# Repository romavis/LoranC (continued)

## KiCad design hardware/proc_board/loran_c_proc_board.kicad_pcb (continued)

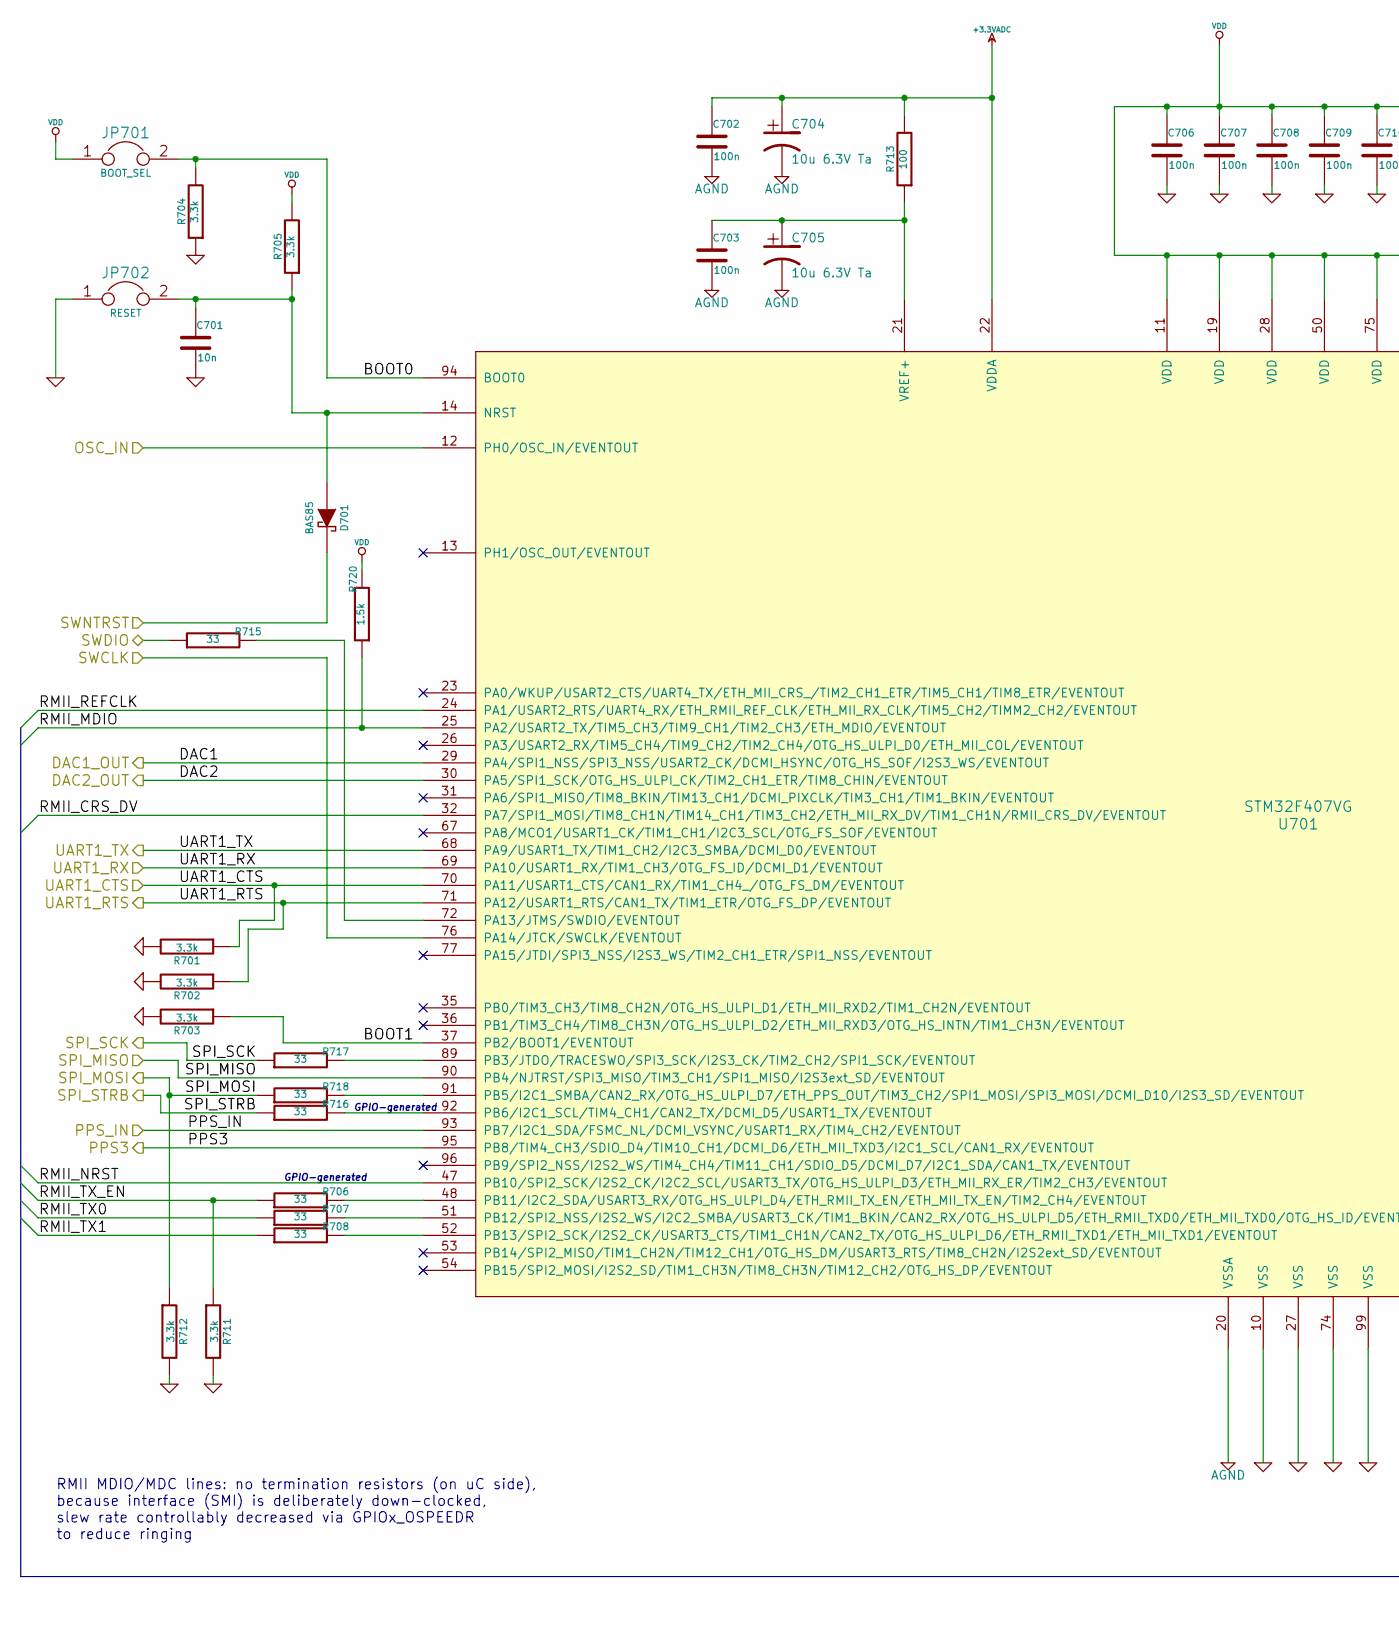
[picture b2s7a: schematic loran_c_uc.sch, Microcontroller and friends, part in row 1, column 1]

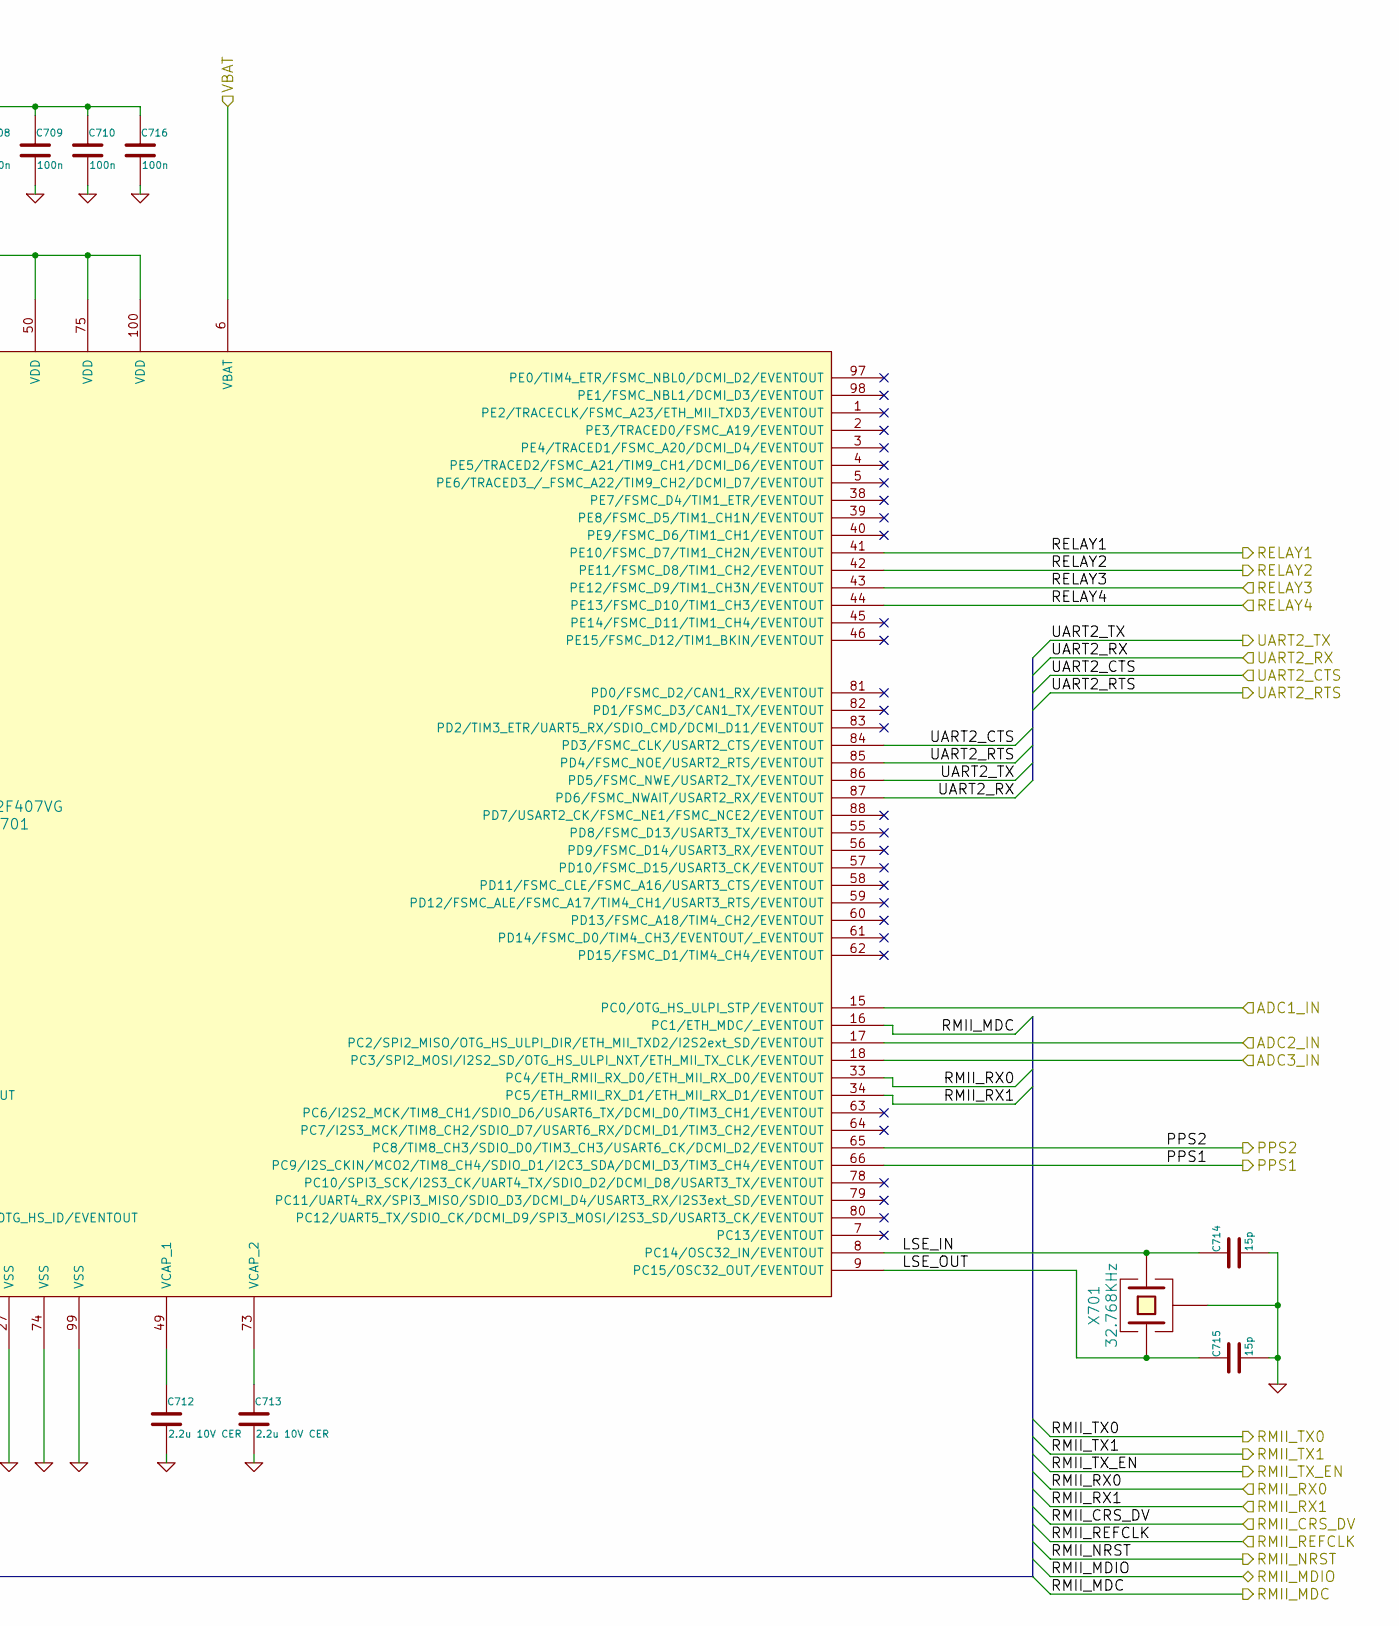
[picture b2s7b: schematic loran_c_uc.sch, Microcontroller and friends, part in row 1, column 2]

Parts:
C701: 10n; c_1206
C702, C703: 100n; c_1206
C704, C705: 10u 6.3V Ta; c_tant_B
C706, C707, C708, C709, C710, C716: 100n; c_0805
C712, C713: 2.2u 10V CER; c_1206
C714, C715: 15p; c_1206
D701: BAS85; sod80c
JP701: BOOT_SEL; Pin_Header_Straight_1x02
JP702: RESET; Pin_Header_Straight_1x02
R701, R702, R705, R711, R712: 3.3k; r_1206
R703, R704: 3.3k; r_0805
R706, R707, R708, R715: 33; r_0805
R713: 100; r_0805
R716, R717, R718: 33; r_1206
R720: 1.5k; r_1206
U701: STM32F407VG; TQFP-100
X701: 32.768KHz; crystal_tc-38_horiz

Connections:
+3.3VADC: C702.1, C704.1, R713.2, U701.22 (VDDA); also elsewhere on the board
/Analog part/DAC1_IN: U701.29 (PA4/SPI1_NSS/SPI3_NSS/USART2_CK/DCMI_HS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); also elsewhere on the board
/Analog part/DAC2_IN: U701.30 (PA5/SPI1_SCK/OTG_HS_ULPI_CK/TIM2_CH1_ET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); also elsewhere on the board
/Ethernet PHY/RMII_CRS_DV: U701.32 (PA7/SPI1_MOSI/TIM8_CH1N/TIM14_CH1/TIM3_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); also elsewhere on the board
/Ethernet PHY/RMII_MDC: U701.16 (PC1/ETH_MDC/_EVENTOUT); also elsewhere on the board
/Ethernet PHY/RMII_MDIO: R720.1, U701.25 (PA2/USART2_TX/TIM5_CH3/TIM9_CH1/TIM2_CH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); also elsewhere on the board
/Ethernet PHY/RMII_NRST: U701.47 (PB10/SPI2_SCK/I2S2_CK/I2C2_SCL/USART3_T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); also elsewhere on the board
/Ethernet PHY/RMII_REFCLK: U701.24 (PA1/USART2_RTS/UART4_RX/ETH_RMII_REF_CL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); also elsewhere on the board
/Ethernet PHY/RMII_RX0: U701.33 (PC4/ETH_RMII_RX_D0/ETH_MII_RX_D0/EVENTO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); also elsewhere on the board
/Ethernet PHY/RMII_RX1: U701.34 (PC5/ETH_RMII_RX_D1/ETH_MII_RX_D1/EVENTO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); also elsewhere on the board
/Ethernet PHY/RMII_TX0: R707.1; also elsewhere on the board
/Ethernet PHY/RMII_TX1: R708.1; also elsewhere on the board
/Ethernet PHY/RMII_TX_EN: R706.1, R711.1; also elsewhere on the board
/RS232 interface/UART1_CTS: R701.1, U701.70 (PA11/USART1_CTS/CAN1_RX/TIM1_CH4_/OTG_F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); also elsewhere on the board
/RS232 interface/UART1_RTS: R702.1, U701.71 (PA12/USART1_RTS/CAN1_TX/TIM1_ETR/OTG_FS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); also elsewhere on the board
/RS232 interface/UART1_RX: U701.69 (PA10/USART1_RX/TIM1_CH3/OTG_FS_ID/DCMI_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); also elsewhere on the board
/RS232 interface/UART1_TX: U701.68 (PA9/USART1_TX/TIM1_CH2/I2C3_SMBA/DCMI_D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); also elsewhere on the board
/RS232 interface/UART2_CTS: U701.84 (PD3/FSMC_CLK/USART2_CTS/EVENTOUT); also elsewhere on the board
/RS232 interface/UART2_RTS: U701.85 (PD4/FSMC_NOE/USART2_RTS/EVENTOUT); also elsewhere on the board
/RS232 interface/UART2_RX: U701.87 (PD6/FSMC_NWAIT/USART2_RX/EVENTOUT); also elsewhere on the board
/RS232 interface/UART2_TX: U701.86 (PD5/FSMC_NWE/USART2_TX/EVENTOUT); also elsewhere on the board
/SPI interface/SPI_MISO: U701.90 (PB4/NJTRST/SPI3_MISO/TIM3_CH1/SPI1_MISO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); also elsewhere on the board
/SPI interface/SPI_MOSI: R712.1, R718.1; also elsewhere on the board
/SPI interface/SPI_SCK: R717.1; also elsewhere on the board
/SPI interface/SPI_STRB: R716.1; also elsewhere on the board
/uC STM32F407/ADC1_IN: U701.15 (PC0/OTG_HS_ULPI_STP/EVENTOUT); also elsewhere on the board
/uC STM32F407/ADC2_IN: U701.17 (PC2/SPI2_MISO/OTG_HS_ULPI_DIR/ETH_MII_T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); also elsewhere on the board
/uC STM32F407/ADC3_IN: U701.18 (PC3/SPI2_MOSI/I2S2_SD/OTG_HS_ULPI_NXT/E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); also elsewhere on the board
/uC STM32F407/BOOT0: JP701.2, R704.2, U701.94 (BOOT0)
/uC STM32F407/BOOT1: R703.1, U701.37 (PB2/BOOT1/EVENTOUT)
/uC STM32F407/LSE_IN: C714.1, U701.8 (PC14/OSC32_IN/EVENTOUT), X701.1
/uC STM32F407/LSE_OUT: C715.1, U701.9 (PC15/OSC32_OUT/EVENTOUT), X701.2
/uC STM32F407/OSC_IN: U701.12 (PH0/OSC_IN/EVENTOUT); also elsewhere on the board
/uC STM32F407/PPS1: U701.66 (PC9/I2S_CKIN/MCO2/TIM8_CH4/SDIO_D1/I2C3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); also elsewhere on the board
/uC STM32F407/PPS2: U701.65 (PC8/TIM8_CH3/SDIO_D0/TIM3_CH3/USART6_CK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); also elsewhere on the board
/uC STM32F407/PPS3: U701.95 (PB8/TIM4_CH3/SDIO_D4/TIM10_CH1/DCMI_D6/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); also elsewhere on the board
/uC STM32F407/PPS_IN: U701.93 (PB7/I2C1_SDA/FSMC_NL/DCMI_VSYNC/USART1_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); also elsewhere on the board
/uC STM32F407/RELAY1: U701.41 (PE10/FSMC_D7/TIM1_CH2N/EVENTOUT); also elsewhere on the board
/uC STM32F407/RELAY2: U701.42 (PE11/FSMC_D8/TIM1_CH2/EVENTOUT); also elsewhere on the board
/uC STM32F407/RELAY3: U701.43 (PE12/FSMC_D9/TIM1_CH3N/EVENTOUT); also elsewhere on the board
/uC STM32F407/RELAY4: U701.44 (PE13/FSMC_D10/TIM1_CH3/EVENTOUT); also elsewhere on the board
/uC STM32F407/SWCLK: U701.76 (PA14/JTCK/SWCLK/EVENTOUT); also elsewhere on the board
/uC STM32F407/SWDIO: R715.1; also elsewhere on the board
/uC STM32F407/SWNTRST: D701.2 (K); also elsewhere on the board
/uC STM32F407/VBAT: U701.6 (VBAT); also elsewhere on the board
AGND: C702.2, C703.2, C704.2, C705.2, U701.20 (VSSA); also elsewhere on the board
GND: C701.2, C706.2, C707.2, C708.2, C709.2, C710.2, C712.2, C713.2, C714.2, C715.2, C716.2, JP702.1, R701.2, R702.2, R703.2, R704.1, R711.2, R712.2, U701.10 (VSS), U701.27 (VSS), U701.74 (VSS), U701.99 (VSS), X701.3; also elsewhere on the board
unnamed: C701.1, D701.1 (A), JP702.2, R705.1, U701.14 (NRST)
unnamed: C703.1, C705.1, R713.1, U701.21 (VREF+)
unnamed: C712.1, U701.49 (VCAP_1)
unnamed: C713.1, U701.73 (VCAP_2)
unnamed: R706.2, U701.48 (PB11/I2C2_SDA/USART3_RX/OTG_HS_ULPI_D4/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)
unnamed: R707.2, U701.51 (PB12/SPI2_NSS/I2S2_WS/I2C2_SMBA/USART3_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)
unnamed: R708.2, U701.52 (PB13/SPI2_SCK/I2S2_CK/USART3_CTS/TIM1_C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)
unnamed: R715.2, U701.72 (PA13/JTMS/SWDIO/EVENTOUT)
unnamed: R716.2, U701.92 (PB6/I2C1_SCL/TIM4_CH1/CAN2_TX/DCMI_D5/U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)
unnamed: R717.2, U701.89 (PB3/JTDO/TRACESWO/SPI3_SCK/I2S3_CK/TIM2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)
unnamed: R718.2, U701.91 (PB5/I2C1_SMBA/CAN2_RX/OTG_HS_ULPI_D7/ET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)
VDD: C706.1, C707.1, C708.1, C709.1, C710.1, C716.1, JP701.1, R705.2, R720.2, U701.11 (VDD), U701.19 (VDD), U701.28 (VDD), U701.50 (VDD), U701.75 (VDD), U701.100 (VDD); also elsewhere on the board

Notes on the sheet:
GPIO-generated
RMII MDIO/MDC lines: no termination resistors (on uC side), because interface (SMI) is deliberately down-clocked, slew rate controllably decreased via GPIOx_OSPEEDR to reduce ringing

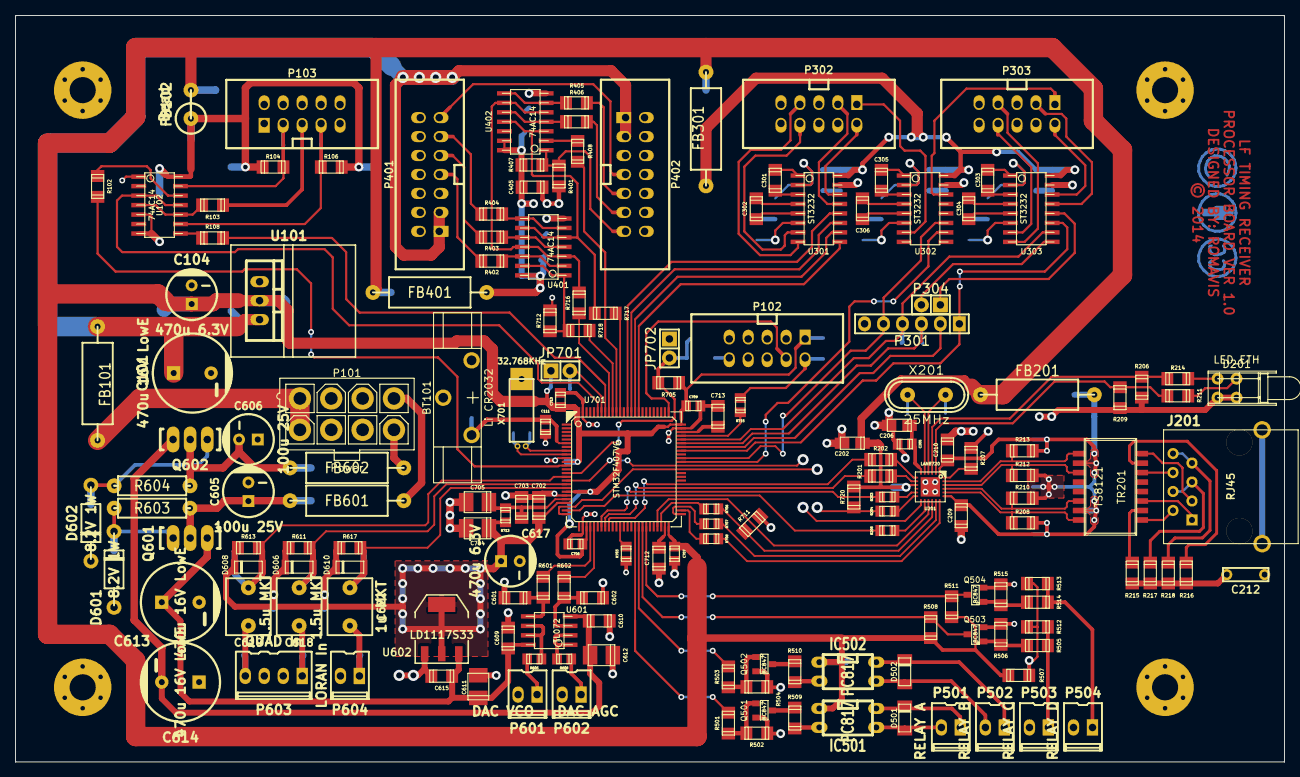
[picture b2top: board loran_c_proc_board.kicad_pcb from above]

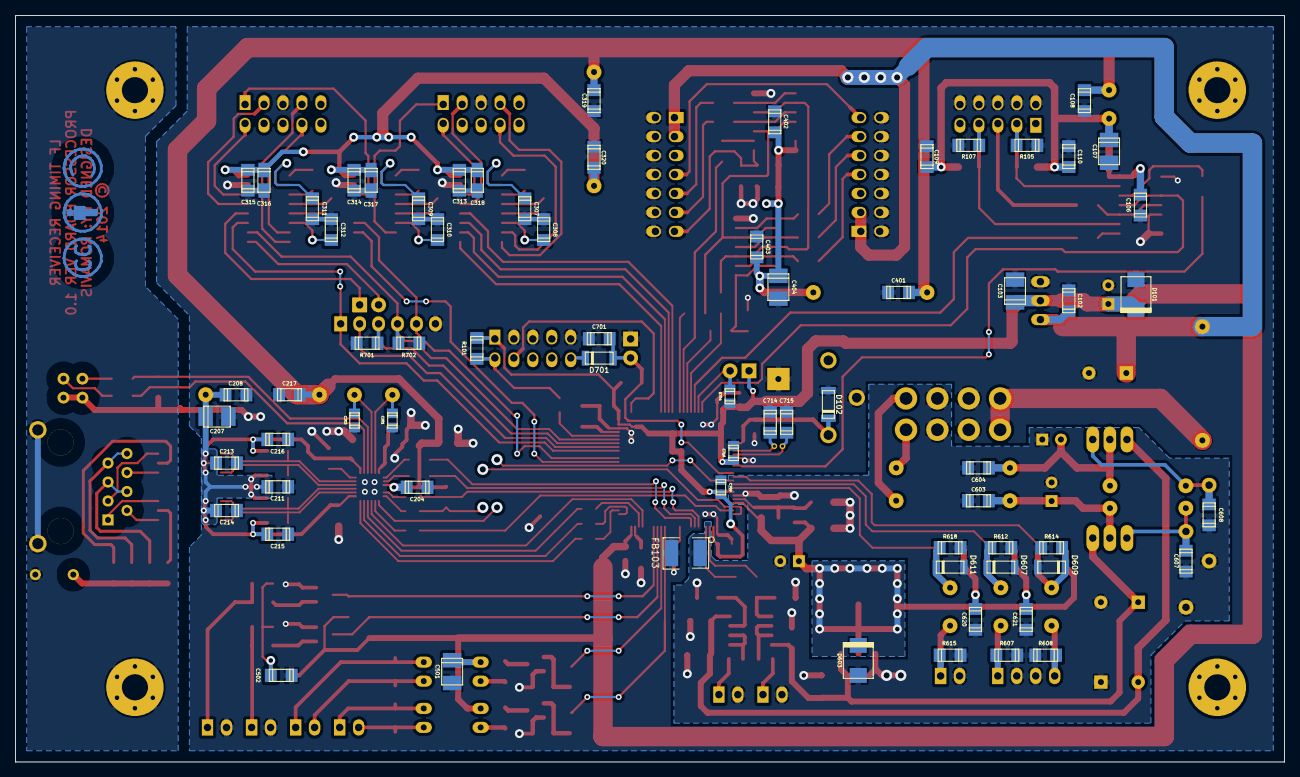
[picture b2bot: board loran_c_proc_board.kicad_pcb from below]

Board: 4 copper layers, 170.0 x 100.0 mm, 243 parts (72 on the bottom side), 173 nets.

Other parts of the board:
LIC1: CC; Symbol_CreativeCommons_CopperTop_Type2_Small
LIC2: BY; Symbol_CC-Attribution_CopperTop_Small
LIC3: SA; Symbol_CC-ShareAlike_CopperTop_Small

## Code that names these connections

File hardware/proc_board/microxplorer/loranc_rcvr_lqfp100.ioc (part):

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Mcu.Name=STM32F407V(E-G)Tx
Mcu.Package=LQFP100
PA1.Mode=RMII
PA1.Signal=ETH_RMII_REF_CLK
PA10.Mode=Hardware-flow-control
PA10.Signal=USART1_RX
PA11.Mode=Hardware-flow-control
PA11.Signal=USART1_CTS
PA12.Mode=Hardware-flow-control
PA12.Signal=USART1_RTS
PA13.Mode=Serial-Wire
PA13.Signal=SYS_JTMS-SWDIO
PA14.Mode=Serial-Wire
PA14.Signal=SYS_JTCK-SWCLK
PA2.Mode=RMII
PA2.Signal=ETH_RMII_MDIO
PA4.Mode=OUT1
PA4.Signal=DAC_OUT1
PA5.Mode=OUT2
PA5.Signal=DAC_OUT2
PA7.Mode=RMII
PA7.Signal=ETH_RMII_CRS_DV
PA9.Mode=Hardware-flow-control
PA9.Signal=USART1_TX
PB10.Signal=GPIO_Output
PB11.Mode=RMII
PB11.Signal=ETH_RMII_TX_EN
PB12.Mode=RMII
PB12.Signal=ETH_RMII_TXD0
PB13.Mode=RMII
PB13.Signal=ETH_RMII_TXD1
PB2.Signal=GPIO_Input
PB3.Mode=Full-Duplex-Master
PB3.Signal=SPI1_SCK
PB4.Mode=Full-Duplex-Master
PB4.Signal=SPI1_MISO
PB5.Mode=Full-Duplex-Master
PB5.Signal=SPI1_MOSI
PB6.Signal=GPIO_Output
PB7.Mode=PWM-Input-2
PB7.Signal=TIM4_CH2
PB8.Signal=TIM4_CH3
PC0.Mode=IN10
PC0.Signal=ADC1_IN10
PC1.Mode=RMII
PC1.Signal=ETH_RMII_MDC
PC14-OSC32_IN.Mode=LSE-External-Oscillator
PC14-OSC32_IN.Signal=SYS_OSC32_IN
PC15-OSC32_OUT.Mode=LSE-External-Oscillator
PC15-OSC32_OUT.Signal=SYS_OSC32_OUT
PC2.Mode=IN12
PC2.Signal=ADC2_IN12
PC3.Mode=IN13
PC3.Signal=ADC3_IN13
PC4.Mode=RMII
PC4.Signal=ETH_RMII_RXD0
PC5.Mode=RMII
PC5.Signal=ETH_RMII_RXD1
PC8.Signal=TIM3_CH3
PC9.Signal=TIM3_CH4
PD3.Mode=Hardware-flow-control
PD3.Signal=USART2_CTS
PD4.Mode=Hardware-flow-control
PD4.Signal=USART2_RTS
PD5.Mode=Hardware-flow-control
PD5.Signal=USART2_TX
PD6.Mode=Hardware-flow-control
PD6.Signal=USART2_RX
PE10.Signal=GPIO_Output
PE11.Signal=GPIO_Output
PE12.Signal=GPIO_Input
PE13.Signal=GPIO_Input
PH0-OSC_IN.Mode=HSE-External-Clock-Source
PH0-OSC_IN.Signal=SYS_OSC_IN

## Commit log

2014-01-18 Initial commit: microcontroller, RS232 and Ethernet PHY are here
2014-01-23 Almost done: SPI, Relay optocouplers, ADC & DAC interface However, bug needs to be fixed: buses are not connected between hierarchical sheets
2014-01-23 FIXED: no more buses on hierarchical sheet ports
2014-01-23 Added: complete schematic in PDF
2014-01-24 Update: fix, assign modules to components -Fix P302 incorrect connection -Assign footprints to components (not all yet) -Back-import footprints into schematic fields
2014-01-24 Fix: broken annotation, sheet numbers, incorrect 74AC14 package
2014-01-25 Update: assign footprint to P101, fix mounting hole symbol (pin # missing)
2014-01-26 Update: minor schematic rework (due to PCB routing), PCB routing in early stage
2014-01-30 Intermediate update: PCB routing/schematic tweaking in process..
2014-02-03 Intermediate update #2: PCB routing/schematic tweaking in process
2014-02-13 Update: lots of refactoring and pin remap ..In chase for easier PCB routing PCB still not completed
2014-02-21 Update: PCB routing still in process...
2014-02-23 Update: PCB almost finished (3D views also up-to-date)
2014-02-24 Update PCB: fix drill diameters (now only 8 required)
2014-02-26 PCB Update: no more tracks underneath SMD 0805, added text
2014-02-26 Directory tree restructured more logically (for future expansion)
2014-02-26 Update: readme and license
2014-02-26 Update: fixed AGND zone on PCB
2014-02-27 PCB prototype production version, minor schematic updates PCB files sent to PCB house. PCB revision as of this commit can be treated as a first (and, hopefully, last) prototype version
2014-02-27 Generate up-to-date 3D renders ..However, with no packages: latest KiCad revision can't handle that properly :-(
2014-03-05 Fix: nice MiniFit connector schematic symbol
2014-03-06 Update: +5V regulator schematic
2014-03-14 Update: added frequecy compensation nets in 5V regulator
2014-03-14 Update: +-15V regulator schematic almost complete
2014-03-15 Update: almost finished power supply schematic (incl. +24V)
2014-03-19 Update: PCB, schematic fixes -Almost completed power supply PCB -Removed discharge resistors from +-15, +24V supplies: no place on PCB for them -Removed ceramic capacitors (stayed in parallel with el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
2014-03-20 Update: PCB gerbers, images. Tagged v0.15
2014-03-21 Update: fix schematic overlapping with page frame, add schematic in PDF
2014-06-05 Added loop antenna preamplifier schematic (built on breadboard now)
2014-06-05 Added RF board (prototype version)
